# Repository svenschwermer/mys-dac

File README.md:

# Audio DAC around the MYS-6ULX-IOT

## UART
Connection diagram for JP1 with a FTDI TTL-232R cable:
1. TX – yellow
1. RX – orange
1. GND – black

## Host PC setup
NetworkManager:
```
nmcli con add \
    type ethernet
    ifname eno1 \
    con-name ethernet-static \
    ipv4.method manual \
    ipv4.addresses 192.168.100.1/24 \
    ipv6.method ignore
```

`/etc/dnsmasq.conf`
```
port=0
interface=eno1
dhcp-range=192.168.100.10,192.168.100.100,12h
enable-tftp
tftp-root=/srv/tftp
```

`/etc/nfs.conf`
```ini
[nfsd]
udp=y
vers2=y
```

`/etc/exports`
```
/srv/nfs/mys_rfs *(rw,no_root_squash,no_subtree_check)
```

## Unmute output
```sh
amixer sset 'Output Mixer HiFi' on
```

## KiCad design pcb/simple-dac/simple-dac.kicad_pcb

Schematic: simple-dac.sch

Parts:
C1, C2, C3, C4, C12, C13, C14: 10µ; C_0805_2012Metric_Pad1.15x1.40mm_HandSolder
C5, C6, C9, C10, C11: 100n; C_0805_2012Metric_Pad1.15x1.40mm_HandSolder
C7, C8: 18p; C_0805_2012Metric_Pad1.15x1.40mm_HandSolder
C15, C16: 220µ; CP_Radial_D6.3mm_P2.50mm; Voltage 10V
H1, H2: MountingHole_Pad; KEYSTONE_7790
J1: Conn_02x07_Odd_Even; TE_MICRO-MATCH_FOB.14P
J2: AudioJack4; SJ-4351X-SMT
R1, R7, R8: 47k; R_0805_2012Metric_Pad1.15x1.40mm_HandSolder
R2, R5, R6: 0; R_0805_2012Metric_Pad1.15x1.40mm_HandSolder
R3: 680; R_0805_2012Metric_Pad1.15x1.40mm_HandSolder
R4: 40k; R_0805_2012Metric_Pad1.15x1.40mm_HandSolder
U1: WM8731; SSOP-28_5.3x10.2mm_P0.65mm
Y1: 11.2896MHz; Crystal_HC49-4H_Vertical

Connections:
+3V3: C2.1, C3.2, C5.1, C6.2, C9.1, C10.1, C12.1, C13.1, J1.2, U1.1, U1.8, U1.14, U1.27
BCLK: J1.8, U1.3
DIN: J1.5, U1.4
DOUT: J1.11, U1.6
GND: C1.1, C2.2, C3.1, C5.2, C6.1, C7.2, C8.2, C9.2, C10.2, C11.2, C12.2, C13.2, C14.2, J1.1, J2.S, R1.2, R7.2, R8.2, U1.11, U1.15, U1.21, U1.22, U1.28
LRCLK: J1.6, R2.2, U1.5
MCLK: J1.10, R6.2
MIC: C1.2, C4.1, J2.R2, R1.1, R3.1
unnamed: C4.2, R4.1
unnamed: C7.1, U1.26, Y1.1
unnamed: C8.1, R5.2, Y1.2
unnamed: C11.1, C14.1, U1.16
unnamed: C15.1, U1.9
unnamed: C15.2, J2.T, R8.1
unnamed: C16.1, U1.10
unnamed: C16.2, J2.R1, R7.1
unnamed: R2.1, U1.7
unnamed: R3.2, U1.17
unnamed: R4.2, U1.18
unnamed: R5.1, R6.1, U1.25
SCL: J1.4, U1.24
SDA: J1.3, U1.23

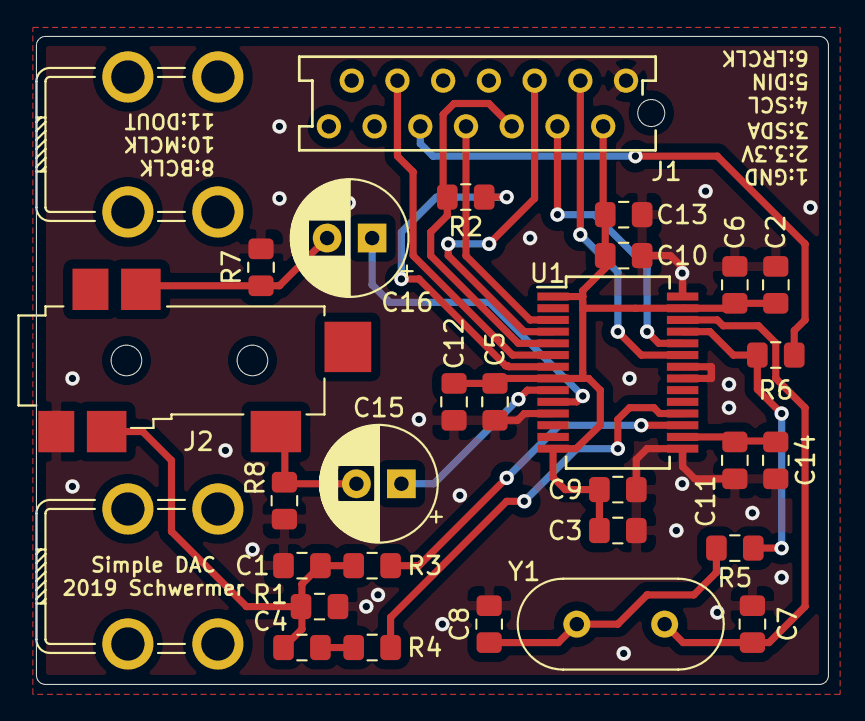
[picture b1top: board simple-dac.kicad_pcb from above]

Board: 2 copper layers, 44.0 x 36.0 mm, 30 parts (0 on the bottom side), 22 nets.

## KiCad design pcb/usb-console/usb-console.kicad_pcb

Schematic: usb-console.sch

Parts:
C1: 10µ; C_0805_2012Metric_Pad1.15x1.40mm_HandSolder
C2, C3: 100n; C_0805_2012Metric_Pad1.15x1.40mm_HandSolder
D1: RED; LED_D3.0mm_Horizontal_O1.27mm_Z2.0mm
D2: GREEN; LED_D3.0mm_Horizontal_O3.81mm_Z6.0mm
H1, H2: MountingHole; KEYSTONE_7790
J1: USB_B_Mini; HIROSE_MX60-MB-5S8
J2: Conn_02x02_Odd_Even; TE_MICRO-MATCH_FOB.04P
R1, R2: R; R_0805_2012Metric_Pad1.15x1.40mm_HandSolder
U1: CH340E; MSOP-10_3x3mm_P0.5mm

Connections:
+5V: C1.1, C2.1, J1.1, J2.1, R2.2, U1.7
/D+: J1.3, U1.1
/D-: J1.2, U1.2
GND: C1.2, C2.2, C3.2, D1.1, D2.1, J1.5, J1.6, J2.4, U1.3
unnamed: C3.1, U1.10
unnamed: D1.2, R1.2
unnamed: D2.2, R2.1
unnamed: J2.2, U1.9
unnamed: J2.3, U1.8
unnamed: R1.1, U1.6

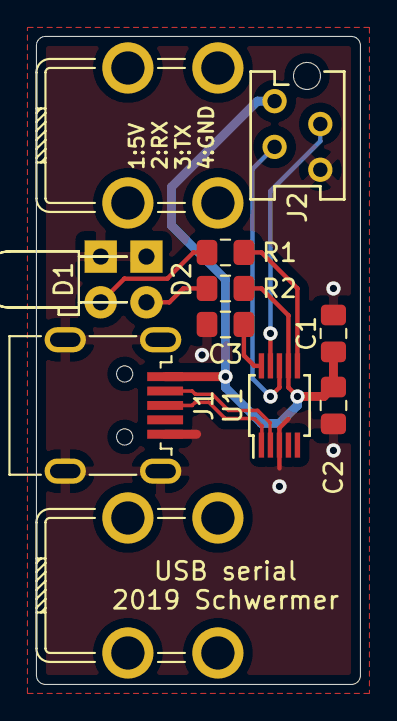
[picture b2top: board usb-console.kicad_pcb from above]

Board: 2 copper layers, 18.0 x 36.0 mm, 12 parts (0 on the bottom side), 10 nets.

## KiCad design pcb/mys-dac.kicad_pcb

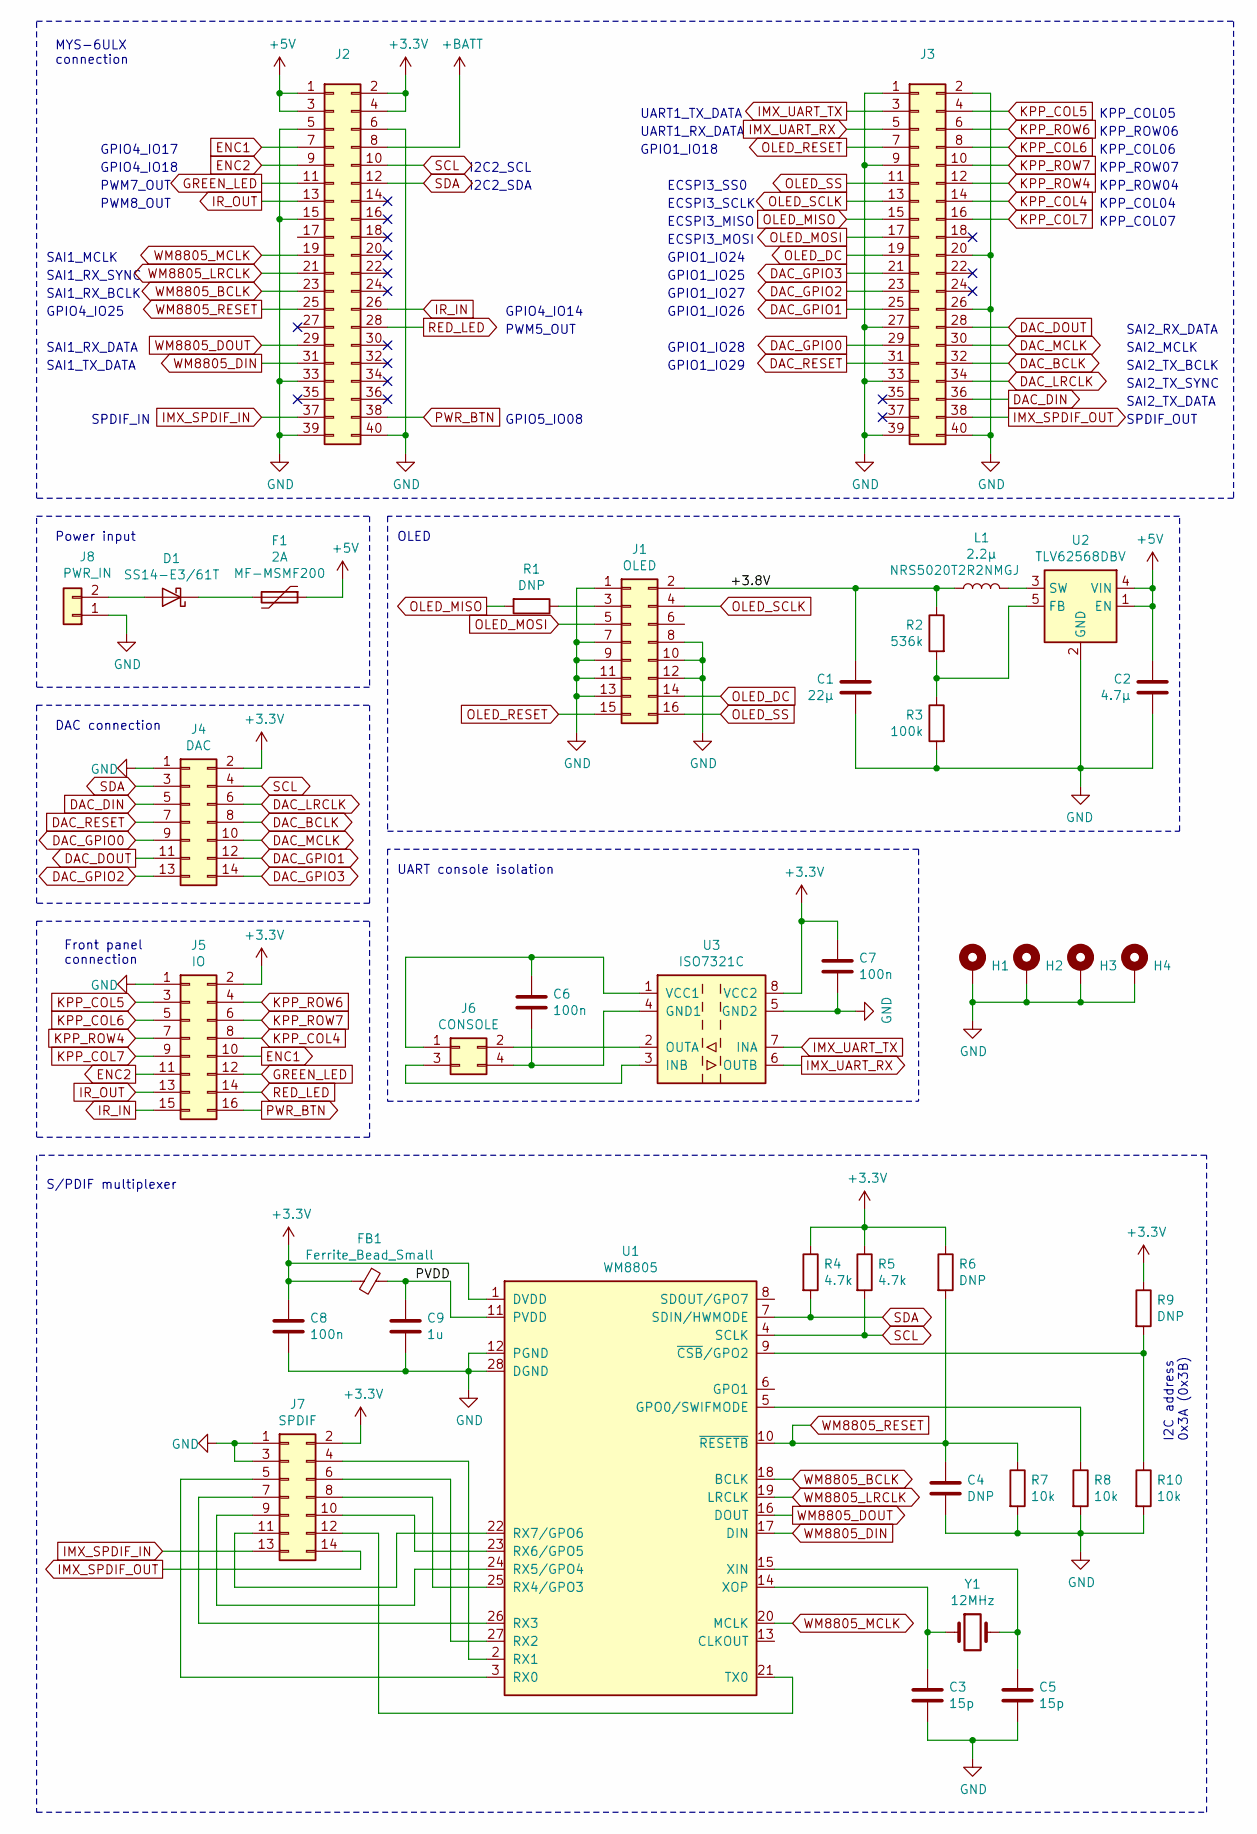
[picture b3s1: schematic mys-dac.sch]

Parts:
C1: 22µ; C_1206_3216Metric_Pad1.42x1.75mm_HandSolder
C2: 4.7µ; C_1206_3216Metric_Pad1.42x1.75mm_HandSolder
C3, C5: 15p; C_0805_2012Metric_Pad1.15x1.40mm_HandSolder
C4: C; C_0805_2012Metric_Pad1.15x1.40mm_HandSolder
C6, C7, C8: 100n; C_0805_2012Metric_Pad1.15x1.40mm_HandSolder
C9: 1u; C_0805_2012Metric_Pad1.15x1.40mm_HandSolder
D1: SS14-E3/61T; D_SMA_Handsoldering
F1: 2A; Fuse_1812_4532Metric_Pad1.30x3.40mm_HandSolder; Part MF-MSMF200
FB1: Ferrite_Bead_Small; L_0805_2012Metric_Pad1.15x1.40mm_HandSolder
H1, H2, H3, H4: MountingHole_Pad; MountingHole_2.5mm_Pad
J1: OLED; TE_MICRO-MATCH_FOB.16P
J2, J3: Conn_02x20_Odd_Even; PinSocket_2x20_P2.00mm_Vertical
J4: DAC; TE_MICRO-MATCH_FOB.14P
J5: IO; TE_MICRO-MATCH_FOB.16P
J6: CONSOLE; TE_MICRO-MATCH_FOB.04P
J7: SPDIF; TE_MICRO-MATCH_FOB.14P
J8: PWR_IN; JST_XH_B2B-XH-A_1x02_P2.50mm_Vertical
L1: 2.2µ; L_Taiyo-Yuden_NR-50xx_HandSoldering; Part NRS5020T2R2NMGJ
R1, R6, R9: R; R_0805_2012Metric_Pad1.15x1.40mm_HandSolder
R2: 536k; R_0805_2012Metric_Pad1.15x1.40mm_HandSolder
R3: 100k; R_0805_2012Metric_Pad1.15x1.40mm_HandSolder
R4, R5: 4.7k; R_0805_2012Metric_Pad1.15x1.40mm_HandSolder
R7, R8, R10: 10k; R_0805_2012Metric_Pad1.15x1.40mm_HandSolder
U1: WM8805; SSOP-28_5.3x10.2mm_P0.65mm
U2: TLV62568DBV; SOT-23-5
U3: ISO7321C; SOIC-8_3.9x4.9mm_P1.27mm
Y1: 12MHz; Crystal_HC49-4H_Vertical

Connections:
+3V3: C7.1, C8.1, FB1.2, J2.2, J2.4, J4.2, J5.2, J7.2, R4.1, R5.1, R6.1, R9.1, U1.1 (DVDD), U3.8 (VCC2)
+5V: C2.1, F1.1, J2.1, J2.3, U2.1 (EN), U2.4 (VIN)
+BATT: J2.8
/+3.8V: C1.1, J1.2, L1.2, R2.1
/PVDD: C9.1, FB1.1, U1.11 (PVDD)
DAC_BCLK: J3.32, J4.8
DAC_DIN: J3.36, J4.5
DAC_DOUT: J3.28, J4.11
DAC_GPIO0: J3.29, J4.9
DAC_GPIO1: J3.25, J4.12
DAC_GPIO2: J3.23, J4.13
DAC_GPIO3: J3.21, J4.14
DAC_LRCLK: J3.34, J4.6
DAC_MCLK: J3.30, J4.10
DAC_RESET: J3.31, J4.7
ENC1: J2.7, J5.10
ENC2: J2.9, J5.11
GND: C1.2, C2.2, C3.2, C4.2, C5.2, C7.2, C8.2, C9.2, H1.1, H2.1, H3.1, H4.1, J1.1, J1.7, J1.8, J1.9, J1.10, J1.11, J1.12, J1.13, J2.5, J2.6, J2.15, J2.33, J2.39, J2.40, J3.1, J3.2, J3.9, J3.20, J3.26, J3.27, J3.33, J3.39, J3.40, J4.1, J5.1, J7.1, J7.3, J8.1, R3.2, R7.2, R8.2, R10.2, U1.12 (PGND), U1.28 (DGND), U2.2 (GND), U3.5 (GND2)
GREEN_LED: J2.11, J5.12
IMX_SPDIF_IN: J2.37, J7.13
IMX_SPDIF_OUT: J3.38, J7.14
IMX_UART_RX: J3.5, U3.6 (OUTB)
IMX_UART_TX: J3.3, U3.7 (INA)
IR_IN: J2.26, J5.15
IR_OUT: J2.13, J5.13
KPP_COL4: J3.14, J5.8
KPP_COL5: J3.4, J5.3
KPP_COL6: J3.8, J5.5
KPP_COL7: J3.16, J5.9
KPP_ROW4: J3.12, J5.7
KPP_ROW6: J3.6, J5.4
KPP_ROW7: J3.10, J5.6
unnamed: C3.1, U1.14 (XOP), Y1.1
unnamed: C5.1, U1.15 (XIN), Y1.2
unnamed: C6.1, J6.1, U3.1 (VCC1)
unnamed: C6.2, J6.4, U3.4 (GND1)
unnamed: D1.1 (K), F1.2
unnamed: D1.2 (A), J8.2
unnamed: J1.3, R1.1
unnamed: J6.2, U3.2 (OUTA)
unnamed: J6.3, U3.3 (INB)
unnamed: J7.4, U1.2 (RX1)
unnamed: J7.5, U1.3 (RX0)
unnamed: J7.6, U1.27 (RX2)
unnamed: J7.7, U1.26 (RX3)
unnamed: J7.8, U1.25 (RX4/GPO3)
unnamed: J7.9, U1.24 (RX5/GPO4)
unnamed: J7.10, U1.23 (RX6/GPO5)
unnamed: J7.11, U1.22 (RX7/GPO6)
unnamed: J7.12, U1.21 (TX0)
unnamed: L1.1, U2.3 (SW)
unnamed: R2.2, R3.1, U2.5 (FB)
unnamed: R8.1, U1.5 (GPO0/SWIFMODE)
unnamed: R9.2, R10.1, U1.9 (~CSB~/GPO2)
OLED_DC: J1.14, J3.19
OLED_MISO: J3.15, R1.2
OLED_MOSI: J1.5, J3.17
OLED_RESET: J1.15, J3.7
OLED_SCLK: J1.4, J3.13
OLED_SS: J1.16, J3.11
PWR_BTN: J2.38, J5.16
RED_LED: J2.28, J5.14
SCL: J2.10, J4.4, R5.2, U1.4 (SCLK)
SDA: J2.12, J4.3, R4.2, U1.7 (SDIN/HWMODE)
WM8805_BCLK: J2.23, U1.18 (BCLK)
WM8805_DIN: J2.31, U1.17 (DIN)
WM8805_DOUT: J2.29, U1.16 (DOUT)
WM8805_LRCLK: J2.21, U1.19 (LRCLK)
WM8805_MCLK: J2.19, U1.20 (MCLK)
WM8805_RESET: C4.1, J2.25, R6.2, R7.1, U1.10 (~RESETB)

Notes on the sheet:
I2C address 0x3A (0x3B)
UART console isolation
OLED
MYS-6ULX connection
PWM7_OUT
SAI1_MCLK
GPIO4_IO18
GPIO4_IO17
PWM8_OUT
SAI1_RX_SYNC
SAI1_RX_BCLK
GPIO4_IO25
SAI1_RX_DATA
SAI1_TX_DATA
SPDIF_IN
I2C2_SCL
GPIO4_IO14
PWM5_OUT
GPIO5_IO08
UART1_TX_DATA
UART1_RX_DATA
GPIO1_IO18
ECSPI3_SS0
ECSPI3_SCLK
ECSPI3_MISO
ECSPI3_MOSI
GPIO1_IO24
GPIO1_IO25
GPIO1_IO27
GPIO1_IO26
GPIO1_IO28
GPIO1_IO29
KPP_COL05
KPP_ROW06
KPP_COL06
KPP_ROW07
KPP_ROW04
KPP_COL04
KPP_COL07
SAI2_RX_DATA

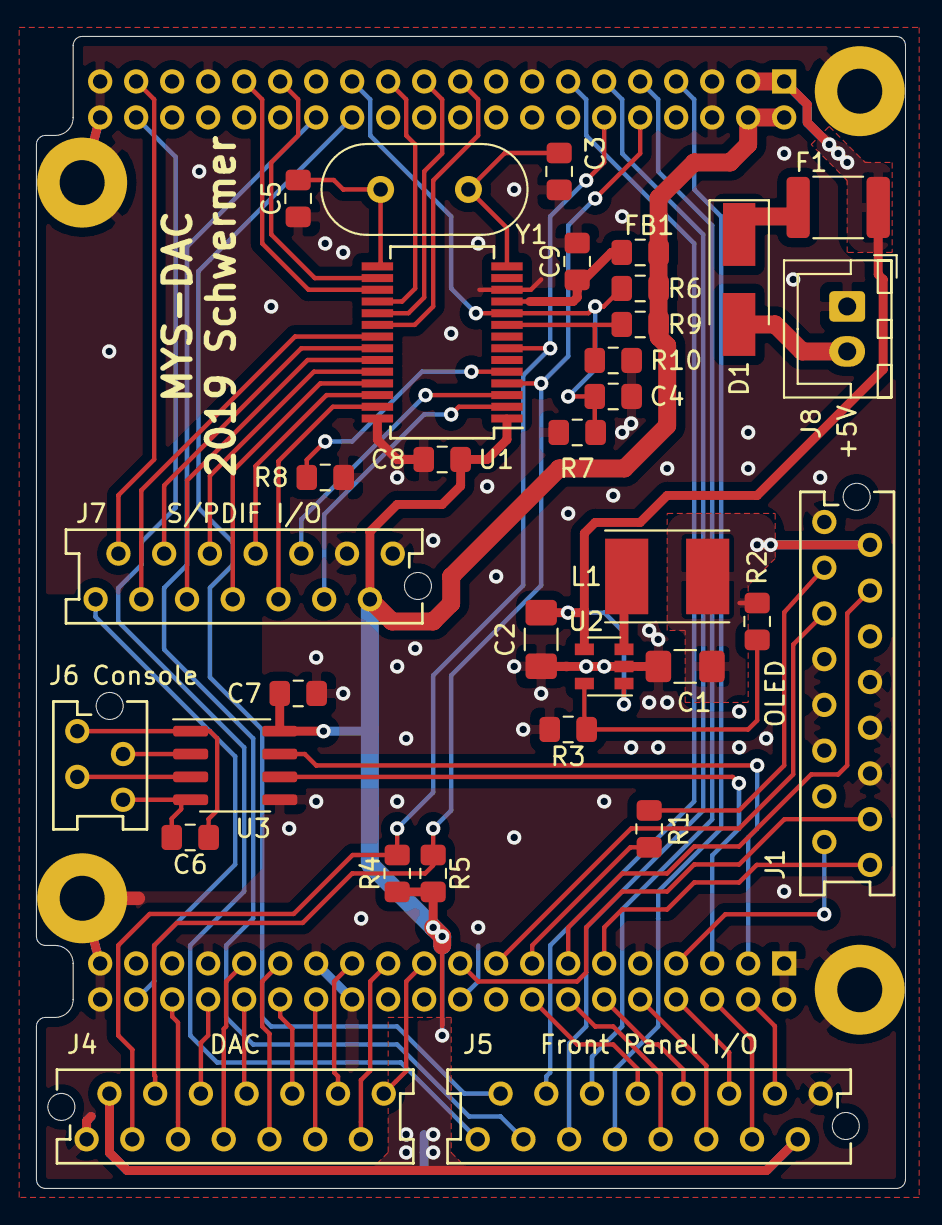
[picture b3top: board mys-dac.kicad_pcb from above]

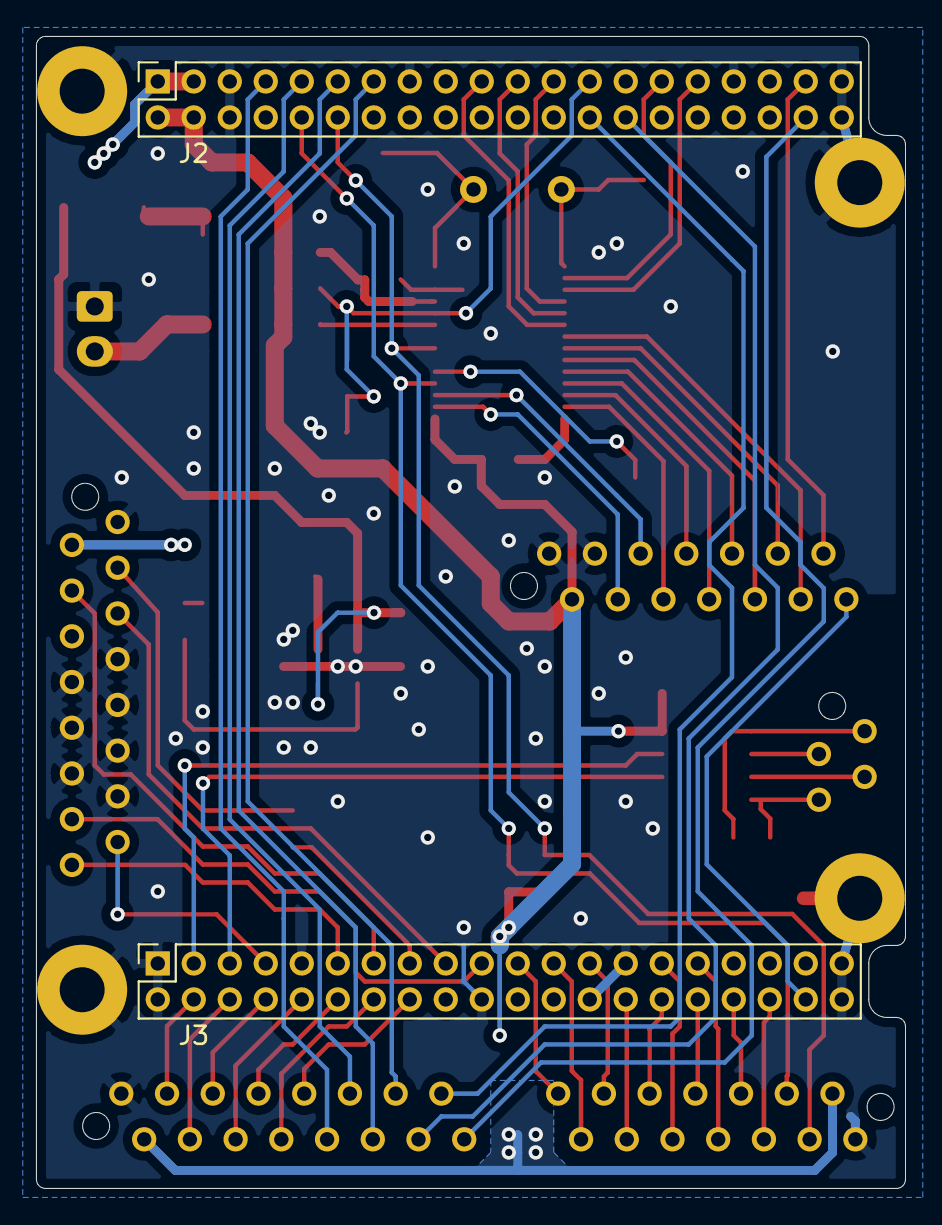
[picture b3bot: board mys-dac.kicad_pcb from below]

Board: 2 copper layers, 48.3 x 64.0 mm, 39 parts (2 on the bottom side), 69 nets.

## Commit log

2019-12-21 Initial
2019-12-23 pcb: Initial state (J2/J3 mixed up)
2019-12-26 Almost completely routed
2019-12-26 Routing complete
2019-12-28 Done routing
2019-12-29 PCBs sent to fab
2019-12-29 Add docs
2019-12-29 Add imx_usb_loader
    The master HEAD contains a regression, so don't use that. See
    https://github.com/boundarydevices/imx_usb_loader/issues/108
2020-01-01 Working NAND boot (SPL & u-boot proper)
    With Linux/DTB (as FIT) and RFS coming via the network.
2020-01-01 MMC functional
2020-02-01 pcb: Update usb-console resistor values
2020-06-13 Fixes for building on Arch
    https://svenschwermer.de/2020/06/12/building-yocto-on-up-to-date-arch-linux.html
2020-06-13 Audio playback via WM8731 functional
2020-06-13 Update u-boot ref
2020-06-13 Add WiFi driver
